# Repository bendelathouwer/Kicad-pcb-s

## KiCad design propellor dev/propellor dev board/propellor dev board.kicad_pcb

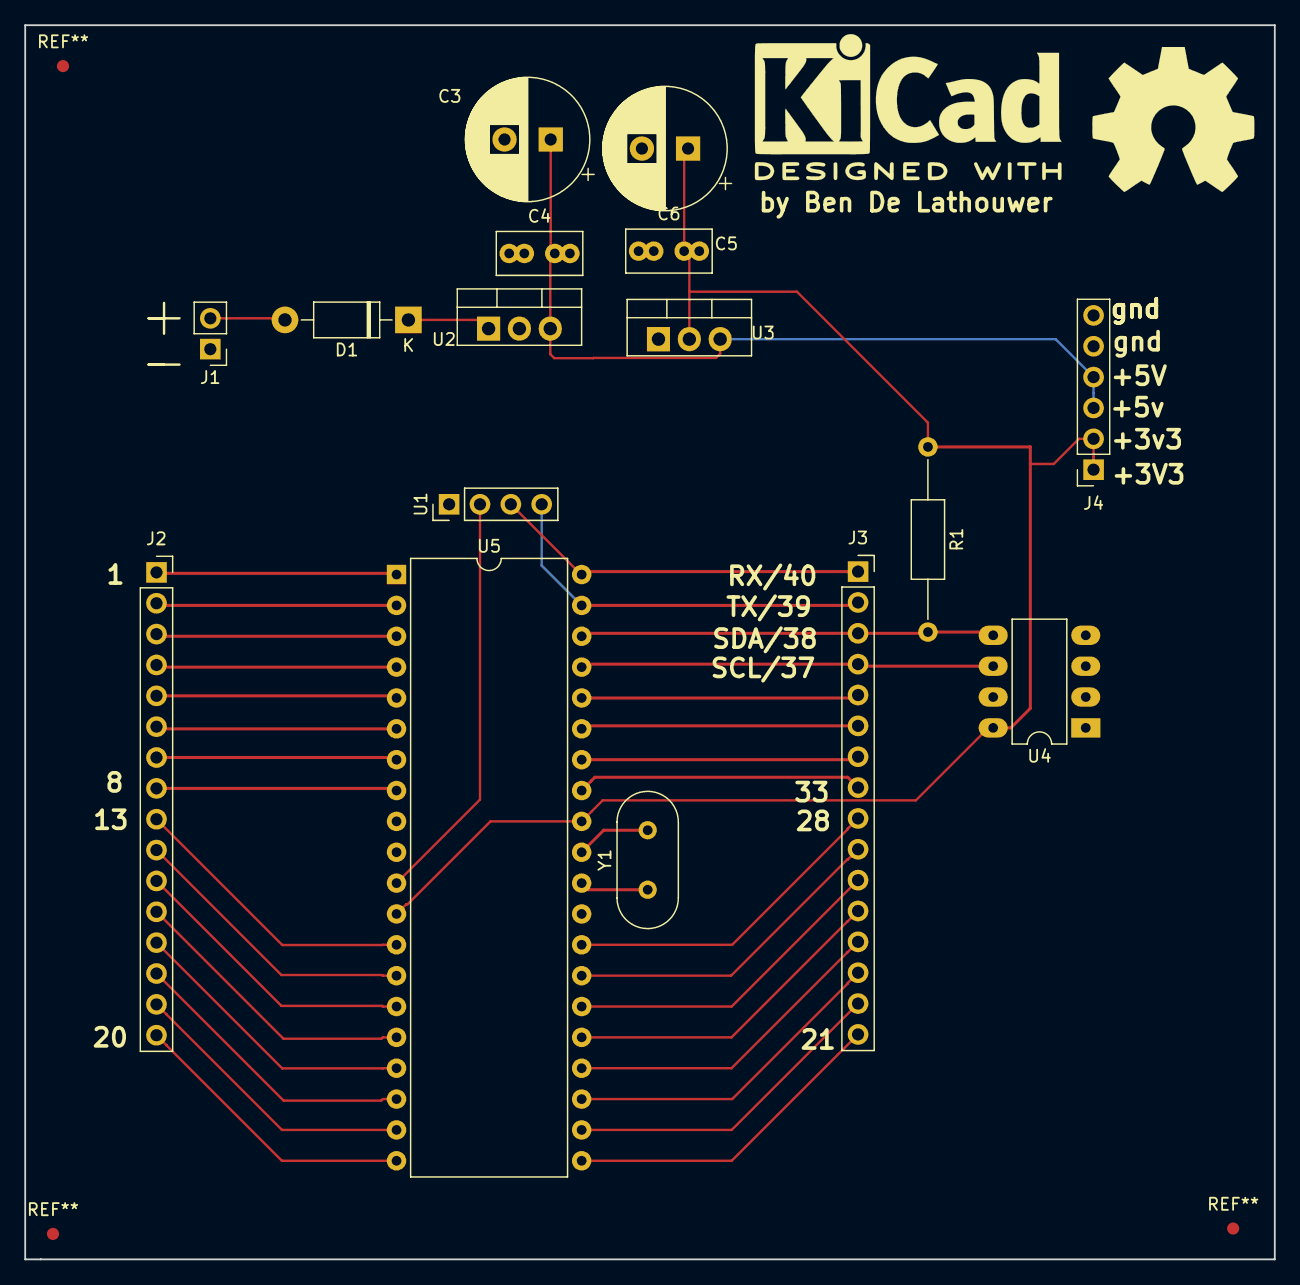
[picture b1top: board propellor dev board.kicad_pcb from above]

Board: 2 copper layers, 102.9 x 101.6 mm, 16 parts (0 on the bottom side), 40 nets.

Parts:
C3, C5: 10u; CP_Radial_D10.0mm_P3.80mm
C4, C6: 100n; C_Rect_L7.0mm_W3.5mm_P2.50mm_P5.00mm
D1: 1N4007; D_DO-41_SOD81_P10.16mm_Horizontal
J1: 2pin header; PinHeader_1x02_P2.54mm_Vertical
J2, J3: Conn_01x16_Male; PinSocket_1x16_P2.54mm_Vertical
J4: Conn_01x06; PinSocket_1x06_P2.54mm_Vertical
R1: 10K; R_Axial_DIN0207_L6.3mm_D2.5mm_P15.24mm_Horizontal
U1: propstick; PinHeader_1x04_P2.54mm_Vertical
U2: LM7805_TO220; TO-220-3_Vertical
U3: LM1117-3.3; TO-220-3_Vertical
U4: 24LC256; DIP-8_W7.62mm_LongPads
U5: P8X32A-D40; DIP-40_W15.24mm
Y1: Crystal_Small; Crystal_HC18-U_Vertical

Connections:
+3V3: C5.1, C6.2, J4.1, J4.2, R1.1, U3.2, U4.8, U5.12, U5.32
+5V: C3.1, C4.2, J4.3, J4.4, U2.3, U3.3
/Rx: J3.1, U1.3, U5.40
/SCL: J3.4, U4.6, U5.37
/SDA: J3.3, R1.2, U4.5, U5.38
/TX: J3.2, U1.4, U5.39
/~res: U1.2, U5.11
GND: C3.2, C4.1, C5.2, C6.1, J1.1, J4.5, J4.6, U1.1, U2.2, U3.1, U4.1, U4.2, U4.3, U4.4, U4.7, U5.9, U5.10, U5.29
unnamed: D1.2, J1.2
unnamed: J2.1, U5.1
unnamed: J2.2, U5.2
unnamed: J2.3, U5.3
unnamed: J2.4, U5.4
unnamed: J2.5, U5.5
unnamed: J2.6, U5.6
unnamed: J2.7, U5.7
unnamed: J2.8, U5.8
unnamed: J2.9, U5.13
unnamed: J2.10, U5.14
unnamed: J2.11, U5.15
unnamed: J2.12, U5.16
unnamed: J2.13, U5.17
unnamed: J2.14, U5.18
unnamed: J2.15, U5.19
unnamed: J2.16, U5.20
unnamed: J3.5, U5.36
unnamed: J3.6, U5.35
unnamed: J3.7, U5.34
unnamed: J3.8, U5.33
unnamed: J3.9, U5.28
unnamed: J3.10, U5.27
unnamed: J3.11, U5.26
unnamed: J3.12, U5.25
unnamed: J3.13, U5.24
unnamed: J3.14, U5.23
unnamed: J3.15, U5.22
unnamed: J3.16, U5.21
unnamed: U5.30, Y1.1
unnamed: U5.31, Y1.2
VAA: D1.1, U2.1

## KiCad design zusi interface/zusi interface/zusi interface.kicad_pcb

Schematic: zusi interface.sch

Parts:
BZ1: Buzzer; Buzzer_Murata_PKMCS0909E4000-R1
C1, C2, C3, C4, C5, C6: C_Small; R_0402_1005Metric
CON1: TAGconnect; Tag-Connect_TC2030-IDC-NL_2x03_P1.27mm_Vertical
D1, D2, D3, D4, D5, D6, D7, D8, D9: LED_Small_ALT; LED_0402_1005Metric
J1: Conn_01x02; Wago_734-132_1x02_P3.50mm_Vertical
JP1, JP2, JP3: SolderJumper_3_Open; SolderJumper-3_P1.3mm_Open_RoundedPad1.0x1.5mm
R1, R2, R3, R5, R6, R7: R; R_0402_1005Metric
R4: R; L_0603_1608Metric
RN1: R_Network07; R_Array_SIP8
U1: PCF8574A; SOIC-16_3.9x9.9mm_P1.27mm
U2: ESP32-WROOM
U3: NCP1117ST33T3G; SOT-223; MPN NCP1117ST33T3G; Digi-Key_PN NCP1117ST33T3GOSCT-ND

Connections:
+3V3: C1.2, C2.1, C3.1, C4.2, CON1.1, JP1.3, JP2.3, JP3.3, R1.1, R4.1, R5.2, R6.2, R7.2, RN1.1, U1.16 (VDD), U2.2, U3.2, U3.4
+12V: C5.2, C6.1, J1.2, U3.3
/Enable: CON1.3, R4.2, U2.3
/GPIO0: CON1.2, R5.1, U2.25
/RX: CON1.4, U2.35
/SCL: R7.1, U1.14 (SCL), U2.36
/SDA: R6.1, U1.15 (SDA), U2.37
/TX: CON1.5, U2.34
/~int: R1.2, U1.13 (~INT~), U2.33
GND: BZ1.2, C1.1, C2.2, C3.2, C4.1, C5.1, C6.2, CON1.6, D8.1, D9.1, J1.1, JP1.1, JP2.1, JP3.1, U1.8 (VSS), U2.1, U2.15, U2.38, U2.39, U3.1
unnamed: BZ1.1, U2.14
unnamed: D1.1, U1.4 (P0)
unnamed: D1.2, RN1.2
unnamed: D2.1, U1.5 (P1)
unnamed: D2.2, RN1.3
unnamed: D3.1, U1.6 (P2)
unnamed: D3.2, RN1.4
unnamed: D4.1, U1.7 (P3)
unnamed: D4.2, RN1.5
unnamed: D5.1, U1.9 (P4)
unnamed: D5.2, RN1.6
unnamed: D6.1, U1.10 (P5)
unnamed: D6.2, RN1.7
unnamed: D7.1, U1.11 (P6)
unnamed: D7.2, RN1.8
unnamed: D8.2, R2.2
unnamed: D9.2, R3.2
unnamed: JP1.2, U1.3 (A2)
unnamed: JP2.2, U1.2 (A1)
unnamed: JP3.2, U1.1 (A0)
unnamed: R2.1, U2.10
unnamed: R3.1, U2.9

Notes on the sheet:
Voeding en ontkopeling
I2C port expander
Wifi+Programming

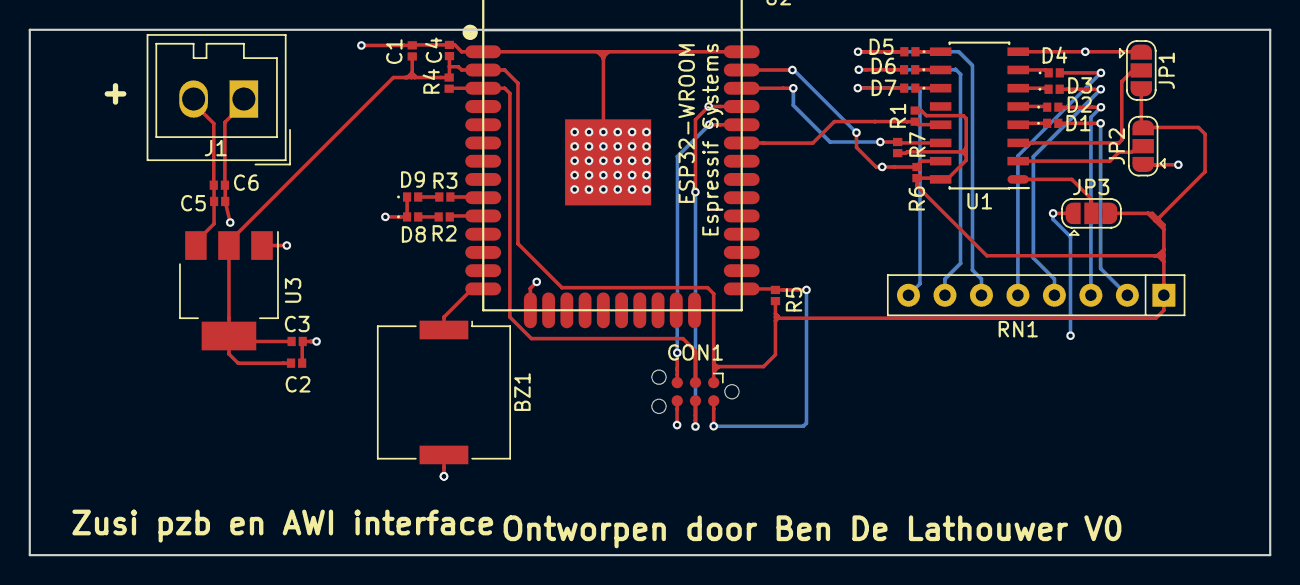
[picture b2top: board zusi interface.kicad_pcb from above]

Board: 2 copper layers, 86.4 x 36.6 mm, 32 parts (0 on the bottom side), 32 nets.

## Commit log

2018-05-11 pcb gelayout zo v3er mogelijk
2018-06-27 prop dev
    aan mijn prop dev board getekend
2018-07-07 pcb done
    pcb afgetekend voor propellor dev board
2018-07-08 af
    3d body's beginnen toevoegen
